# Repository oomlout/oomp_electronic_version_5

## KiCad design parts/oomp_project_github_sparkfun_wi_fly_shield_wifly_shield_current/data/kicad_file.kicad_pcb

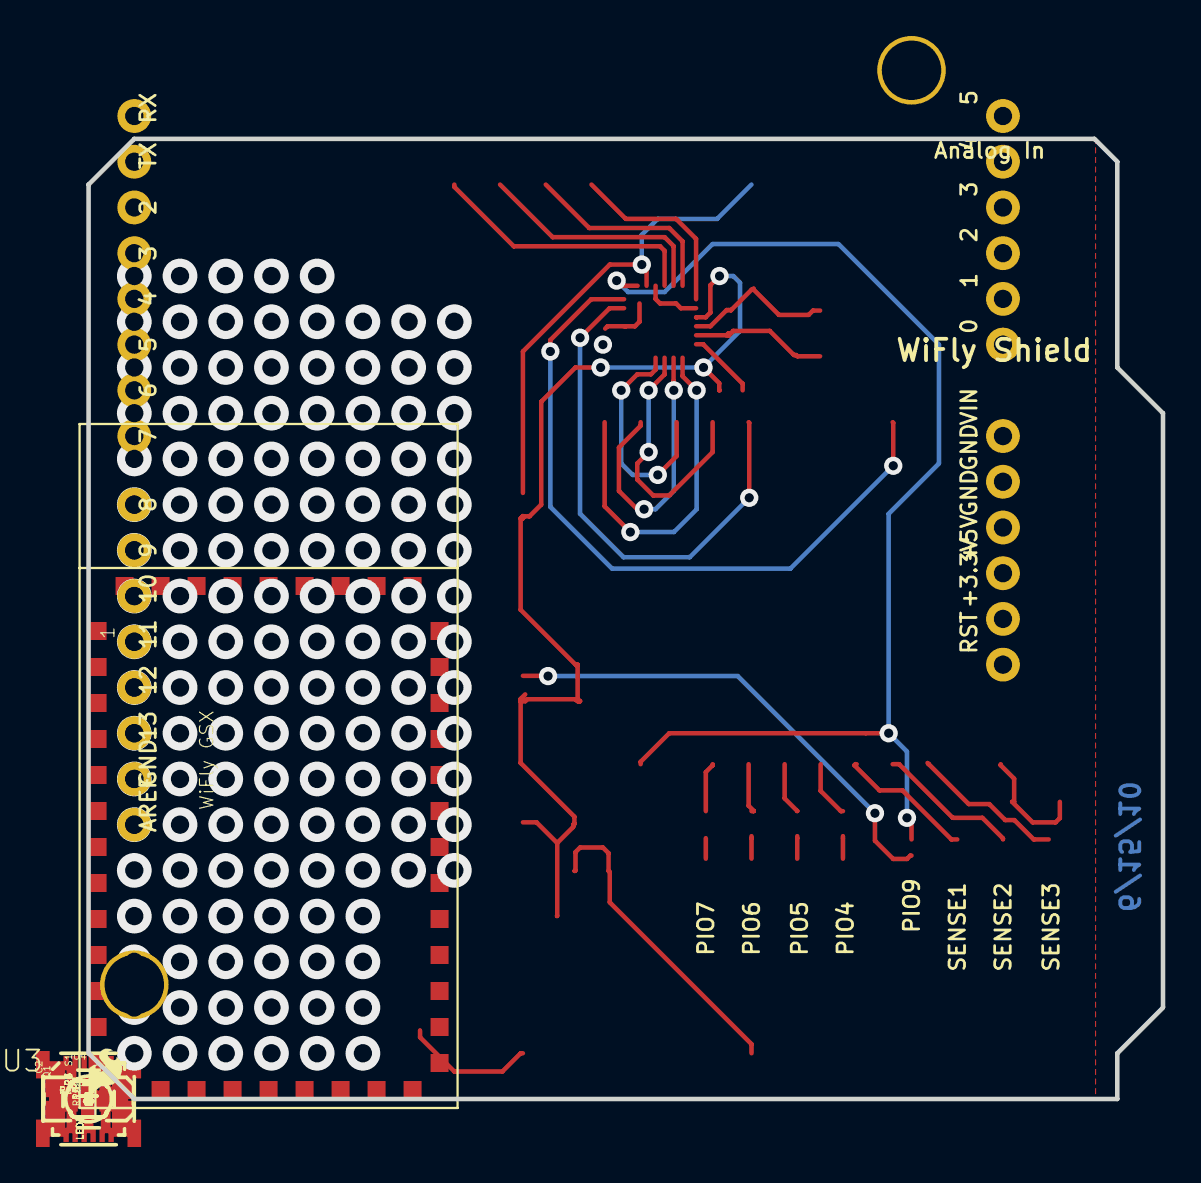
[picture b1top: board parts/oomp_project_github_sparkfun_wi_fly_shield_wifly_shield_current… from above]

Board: 2 copper layers, 59.7 x 53.3 mm, 33 parts (1 on the bottom side), 32 nets.

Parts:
C1: 0.1uF; 0402-CAP
C2: 10uF; EIA3216
C3, C4: 18pF; 0402-CAP
JP1, JP2, JP3, JP4: SJ_2S-NO
JP6: LOGO-SFENEW; SFE-NEW-WEBLOGO
JP7, JP8: FIDUCIAL1X2; FIDUCIAL-1X2
JP9: LOGO-SFESK; SFE-LOGO-FLAME
LED1: BLUE; LED-0603
LED2: YELLOW; LED-0603
LED3: RED; LED-0603
LED4: GREEN; LED-0603
Q1: 14.7456MHz; CRYSTAL-SMD-5X3
R1: 22k; 0402-RES
R2: 10k; 0402-RES
R3: 49k; 0402-RES
R4, R5, R6, R7: 220; 0402-RES
R8, R10: 1k; 0402-RES
R9: 1M; 0402-RES
S1: TACTILE_SWITCH_SMD
U1: ARDUINO_SHIELD; DUEMILANOVE_SHIELD
U2: WIFLY_GSX
U3: SC16IS750; QFN-24
U4: 3.3V; SOT23-5
U$1: CREATIVE_COMMONS

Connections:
3.3V: C1.2, C2.A, R3.2, R8.2, R10.2, U2.20, U2.21, U3.4, U4.5
CS: U1.D10, U3.6
CTS: U2.11, U3.21
D7: R10.1, U1.D7, U3.11
FW: U2.9, U3.14
GND: C1.1, C2.C, C3.2, C4.2, JP1.2, JP2.2, JP3.2, R2.1, R4.1, R5.1, R6.1, R7.1, S1.3, U1.GND@0, U1.GND@1, U1.GND@2, U2.18, U2.19, U2.36, U2.37, U2.38, U2.39, U2.40, U2.41, U2.42, U2.43, U2.44, U3.5, U3.10, U3.16, U4.2
MISO: U1.D12, U3.8
MOSI: U1.D11, U3.7
unnamed: LED4.C, R7.2
unnamed: JP4.2, R3.1
unnamed: LED3.C, R6.2
unnamed: LED2.C, R5.2
unnamed: LED1.C, R4.2
unnamed: U2.13, U3.24
unnamed: U2.12, U3.23
unnamed: R8.1, U3.1
unnamed: C3.1, Q1.1, R9.1, U3.3
unnamed: C4.1, Q1.3, R9.2, U3.2
unnamed: R1.1, R2.2, U2.34
PIO4: LED4.A, U2.29
PIO5: LED3.A, U2.28
PIO6: LED2.A, U2.27
PIO7: LED1.A, U2.26
PIO9: JP4.1, U2.24, U3.12
RES: S1.1, U1.RES
RL: U2.5, U3.13
RTS: U2.10, U3.22
SCLK: U1.D13, U3.9
SENS1: JP1.1, U2.30
SENS2: JP2.1, U2.31
SENS3: JP3.1, U2.32
VIN: U1.VIN, U4.1, U4.3

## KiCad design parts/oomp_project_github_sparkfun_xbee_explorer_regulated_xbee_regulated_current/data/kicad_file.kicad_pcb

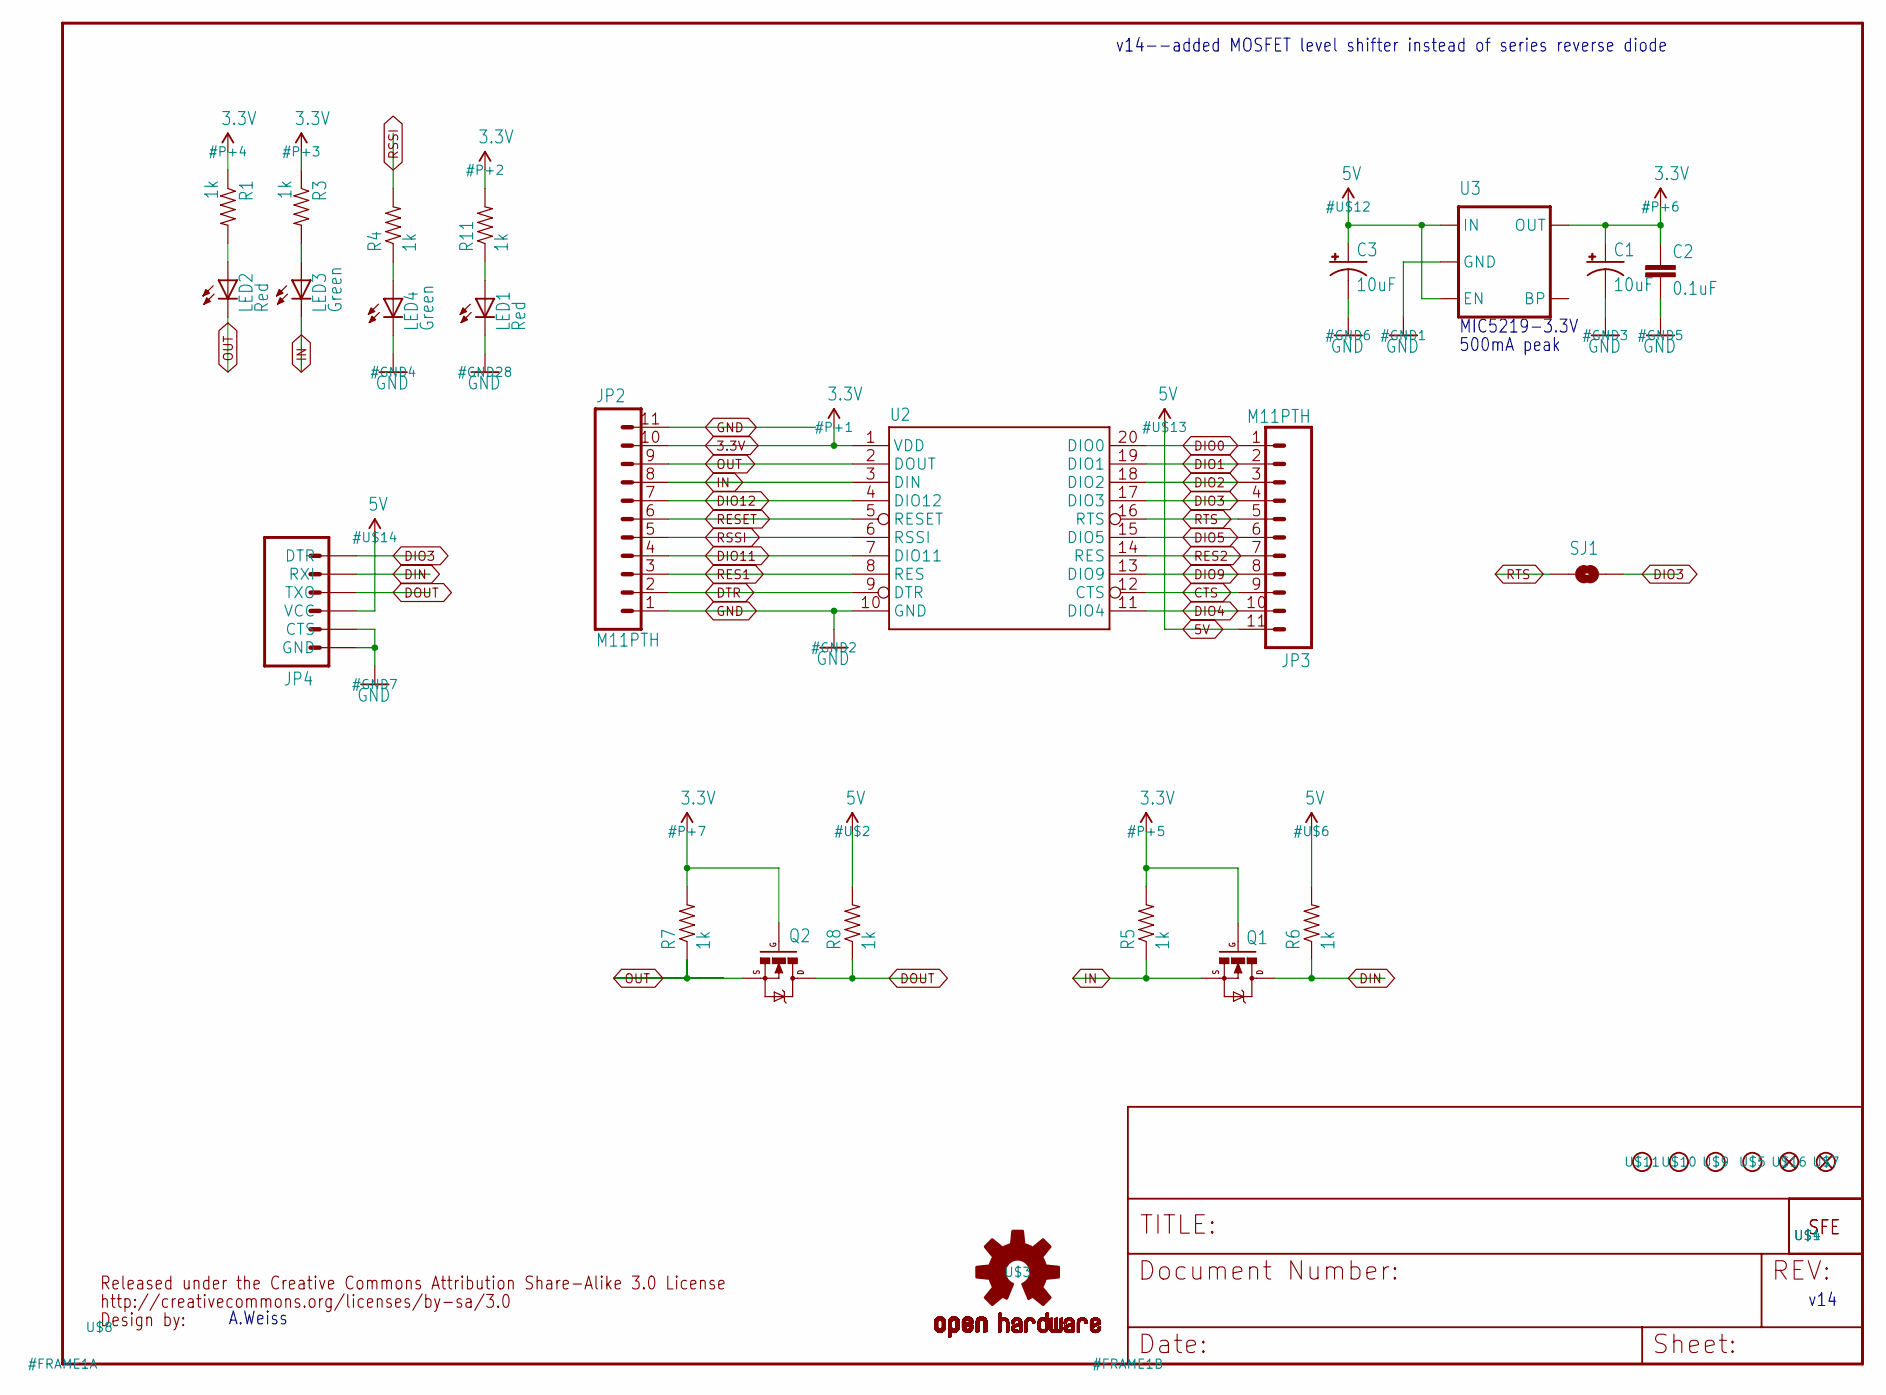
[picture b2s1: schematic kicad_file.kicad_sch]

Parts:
C1, C3: 10uF; EIA3216
C2: 0.1uF; 0402-CAP
JP2, JP3: M11PTH; 1X11
JP4: ARDUINO_SERIAL_PROGRAMPTH; 1X06
LED1, LED2: Red; LED-0603
LED3, LED4: Green; LED-0603
Q1, Q2: MOSFET-NCHANNELSMD; SOT23-3
R1, R3, R4, R5, R6, R7, R8, R11: 1k; 0402-RES
SJ1: SOLDERJUMPERNO; SJ_2S-NO
U2: XBEE-1B3; XBEE-SMD
U3: V_REG_LDOSMD; SOT23-5
U$1: LOGO-SFESK; SFE-LOGO-FLAME
U$3: OSHW-LOGOS; OSHW-LOGO-S
U$4: LOGO-SFENEW; SFE-NEW-WEBLOGO
U$5, U$9, U$10, U$11: STAND-OFF
U$7, U$16: FIDUCIAL1X2; FIDUCIAL-1X2
U$8: CREATIVE_COMMONS

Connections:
3.3V: C1.A (+), C2.1, JP2.10, Q1.1 (G), Q2.1 (G), R1.1, R3.1, R5.2, R7.2, R11.2, U2.1 (VDD), U3.5 (OUT)
5V: C3.A (+), JP3.11, JP4.4 (VCC), R6.2, R8.2, U3.1 (IN), U3.3 (EN)
CTS: JP3.9, U2.12 (CTS)
DIN: JP4.2 (RXI), Q1.3 (D), R6.1
DIO0: JP3.1, U2.20 (DIO0)
DIO1: JP3.2, U2.19 (DIO1)
DIO2: JP3.3, U2.18 (DIO2)
DIO3: JP3.4, JP4.1 (DTR), SJ1.2, U2.17 (DIO3)
DIO4: JP3.10, U2.11 (DIO4)
DIO5: JP3.6, U2.15 (DIO5)
DIO9: JP3.8, U2.13 (DIO9)
DIO11: JP2.4, U2.7 (DIO11)
DIO12: JP2.7, U2.4 (DIO12)
DOUT: JP4.3 (TXO), Q2.3 (D), R8.1
DTR: JP2.2, U2.9 (DTR)
GND: C1.C (-), C2.2, C3.C (-), JP2.1, JP2.11, JP4.5 (CTS), JP4.6 (GND), LED1.C, LED4.C, U2.10 (GND), U3.2 (GND)
IN: JP2.8, LED3.C, Q1.2 (S), R5.1, U2.3 (DIN)
unnamed: LED2.A, R1.2
unnamed: LED4.A, R4.1
unnamed: LED3.A, R3.2
unnamed: LED1.A, R11.1
OUT: JP2.9, LED2.C, Q2.2 (S), R7.1, U2.2 (DOUT)
RES1: JP2.3, U2.8 (RES)
RES2: JP3.7, U2.14 (RES)
RESET: JP2.6, U2.5 (RESET)
RSSI: JP2.5, R4.2, U2.6 (RSSI)
RTS: JP3.5, SJ1.1, U2.16 (RTS)

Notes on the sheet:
MIC5219-3.3V
v14--added MOSFET level shifter instead of series reverse diode
A.Weiss
v14
500mA peak

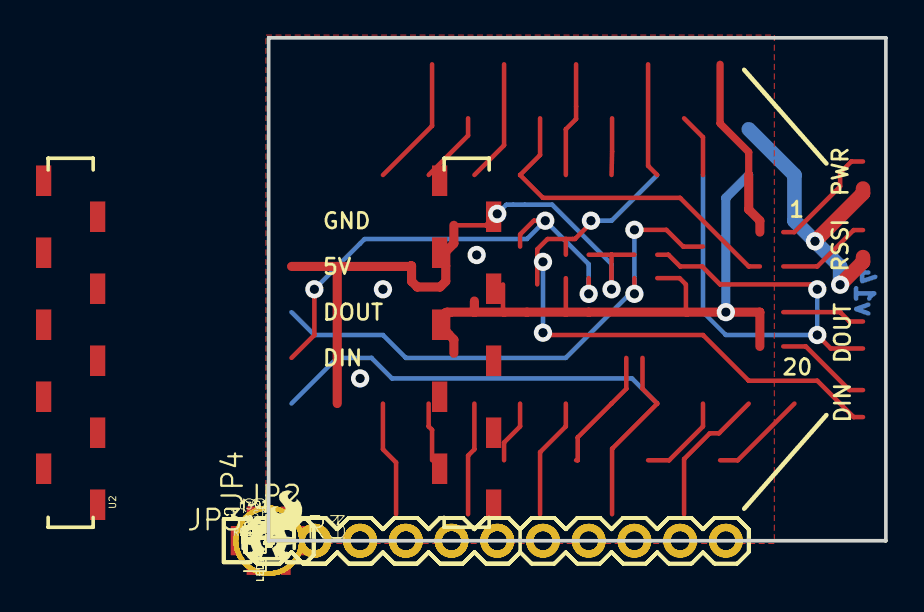
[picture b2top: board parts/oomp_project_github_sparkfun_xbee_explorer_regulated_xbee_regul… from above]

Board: 2 copper layers, 34.3 x 27.9 mm, 33 parts (1 on the bottom side), 27 nets.

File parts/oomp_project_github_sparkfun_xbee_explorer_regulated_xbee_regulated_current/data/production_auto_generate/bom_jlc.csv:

Comment,Designator,Footprint,LCSC Part #
,JP4,XBee-Regulated-import-fps:1X06,C37208
0.1uF,C2,XBee-Regulated-import-fps:0402-CAP,C60474
10uF,"C1,C3",XBee-Regulated-import-fps:EIA3216,
1k,"R1,R3,R4,R5,R6,R7,R8,R11",XBee-Regulated-import-fps:0402-RES,C2906864
CREATIVE_COMMONS,U$8,XBee-Regulated-import-fps:CREATIVE_COMMONS,
FIDUCIAL1X2,"U$7,U$16",XBee-Regulated-import-fps:FIDUCIAL-1X2,
Green,"LED3,LED4",XBee-Regulated-import-fps:LED-0603,
LOGO-SFENEW,U$4,XBee-Regulated-import-fps:SFE-NEW-WEBLOGO,
LOGO-SFESK,U$1,XBee-Regulated-import-fps:SFE-LOGO-FLAME,
M11PTH,"JP2,JP3",XBee-Regulated-import-fps:1X11,C2894934
MOSFET-NCHANNELSMD,"Q1,Q2",XBee-Regulated-import-fps:SOT23-3,
OSHW-LOGOS,U$3,XBee-Regulated-import-fps:OSHW-LOGO-S,
Red,"LED1,LED2",XBee-Regulated-import-fps:LED-0603,
V_REG_LDOSMD,U3,XBee-Regulated-import-fps:SOT23-5,
XBEE-1B3,U2,XBee-Regulated-import-fps:XBEE-SMD,

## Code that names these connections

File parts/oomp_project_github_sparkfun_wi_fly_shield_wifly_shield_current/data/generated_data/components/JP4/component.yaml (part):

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        pin_name: XTAL2
      - reference: JP1
        pin_number: '21'
        pin_name: /RTS
      - reference: JP1
        pin_number: '22'
        pin_name: /CTS
      - reference: JP2
        pin_number: '1'
        pin_name: RESET
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        pin_name: XTAL2
      - reference: JP2
        pin_number: '21'
        pin_name: /RTS
      - reference: JP2
        pin_number: '22'
        pin_name: /CTS
      - reference: JP2
        pin_number: '23'
        pin_name: TX
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        pin_name: XTAL2
      - reference: JP3
        pin_number: '21'
        pin_name: /RTS
      - reference: JP3
        pin_number: '22'
        pin_name: /CTS
      - reference: JP3
        pin_number: '23'
        pin_name: TX
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      no_connect: false
      connected_to: []
    - number: '18'
      name: GPIO5-/DTR
      electrical_type: bidirectional
      graphic_style: line
      local_position:
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        pin_name: RESET
      - reference: JP4
        pin_number: '22'
        pin_name: /CTS
      - reference: JP4
        pin_number: '24'
        pin_name: RX
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        pin_name: RESET
      - reference: JP4
        pin_number: '22'
        pin_name: /CTS
      - reference: JP4
        pin_number: '23'
        pin_name: TX
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    pin_name: XTAL1
  - reference: JP1
    pin_number: '21'
    pin_name: /RTS
  - reference: JP1
    pin_number: '22'
    pin_name: /CTS
  - reference: JP1
    pin_number: '24'
    pin_name: RX
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    pin_name: XTAL1
  - reference: JP2
    pin_number: '21'
    pin_name: /RTS
  - reference: JP2
    pin_number: '22'
    pin_name: /CTS
  - reference: JP2
    pin_number: '23'
    pin_name: TX
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    pin_name: XTAL1
  - reference: JP3
    pin_number: '21'
    pin_name: /RTS
  - reference: JP3
    pin_number: '22'
    pin_name: /CTS
  - reference: JP3
    pin_number: '23'
    pin_name: TX
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    pin_name: XTAL2
  - reference: JP4
    pin_number: '22'
    pin_name: /CTS
  - reference: JP4
    pin_number: '23'
    pin_name: TX
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

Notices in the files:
parts/oomp_project_github_sparkfun_wi_fly_shield_wifly_shield_current/data/original/kicad_file.kicad_sch:
Released under the Creative Commons Attribution Share-Alike 3.0 License
http://creativecommons.org/licenses/by-sa/3.0
parts and their libraries:
Creative Commons License summary
